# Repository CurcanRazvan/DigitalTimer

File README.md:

# Digital Timer - University Practice Project

This is the project I built for my 2nd-year university practice module. It is a digital timer designed in KiCad, capable of counting seconds (0-59) and displaying them on two 7-segment displays.

### Technical Overview

The circuit is designed with a modular approach:
1.  **Clock Signal:** Generated by an **NE555** timer configured as an astable oscillator.
2.  **Counting:** Handled by two **74LS193** 4-bit synchronous binary counters (U7 and U8).
3.  **Decoding & Display:** The binary signal is converted for the 7-segment displays using **CD4511** decoders.

**Logic Control:**
I used additional logic gates (**74LS73, 74LS08, CD4071**) to handle the counting limit (resetting at 60) and the Up/Down direction control.

### Schematic
Here is the final schematic, which includes the corrections needed for everything to work properly:

### v1.0 & Debugging

After getting the PCB manufactured and soldering the components, I spotted a mistake in the initial schematic: Pin 11 (Load) on the counters wasn't connected to 5V, and the C4 capacitor (47uF) wasn't linked to resistor R17.

**The Fix:**
I fixed this directly on the board by adding two jumper wires on the bottom layer.
* The red wires visible in the photo below connect the pins to 5V and route the capacitor correctly.
* With these changes, the circuit works perfectly.

| Top Layer (Components) | Bottom Layer (The Red Wire Fix) |
|:---:|:---:|
|  |  |

### Bill of Materials (BOM)

The total cost for the project (components + PCB + shipping) was approximately 140 Lei (~$30).

| Ref | Component | Description |
|:---|:---|:---|
| U9 | **NE555P** | Precision Timer |
| U7, U8 | **SN74LS193N** | Sync Binary Counter UP/DOWN |
| U6, U10 | **CD4511BE** | BCD to 7-Segment Decoder |
| U5, U11 | **HDSP-5601** | 7-Segment Display |
| U1 | **L7805** | 5V Voltage Regulator |
| U2 | **SN74LS73AN** | Dual JK Flip-Flop |
| U3 | **SN74LS08N** | Quad 2-Input AND Gate |
| U4 | **CD4071BE** | Quad 2-Input OR Gate |
| - | **9V Battery** | Power Source |

### Repository Structure
* `/kicad` - Source files (.sch, .kicad_pcb)
* `/img` - Images and renders

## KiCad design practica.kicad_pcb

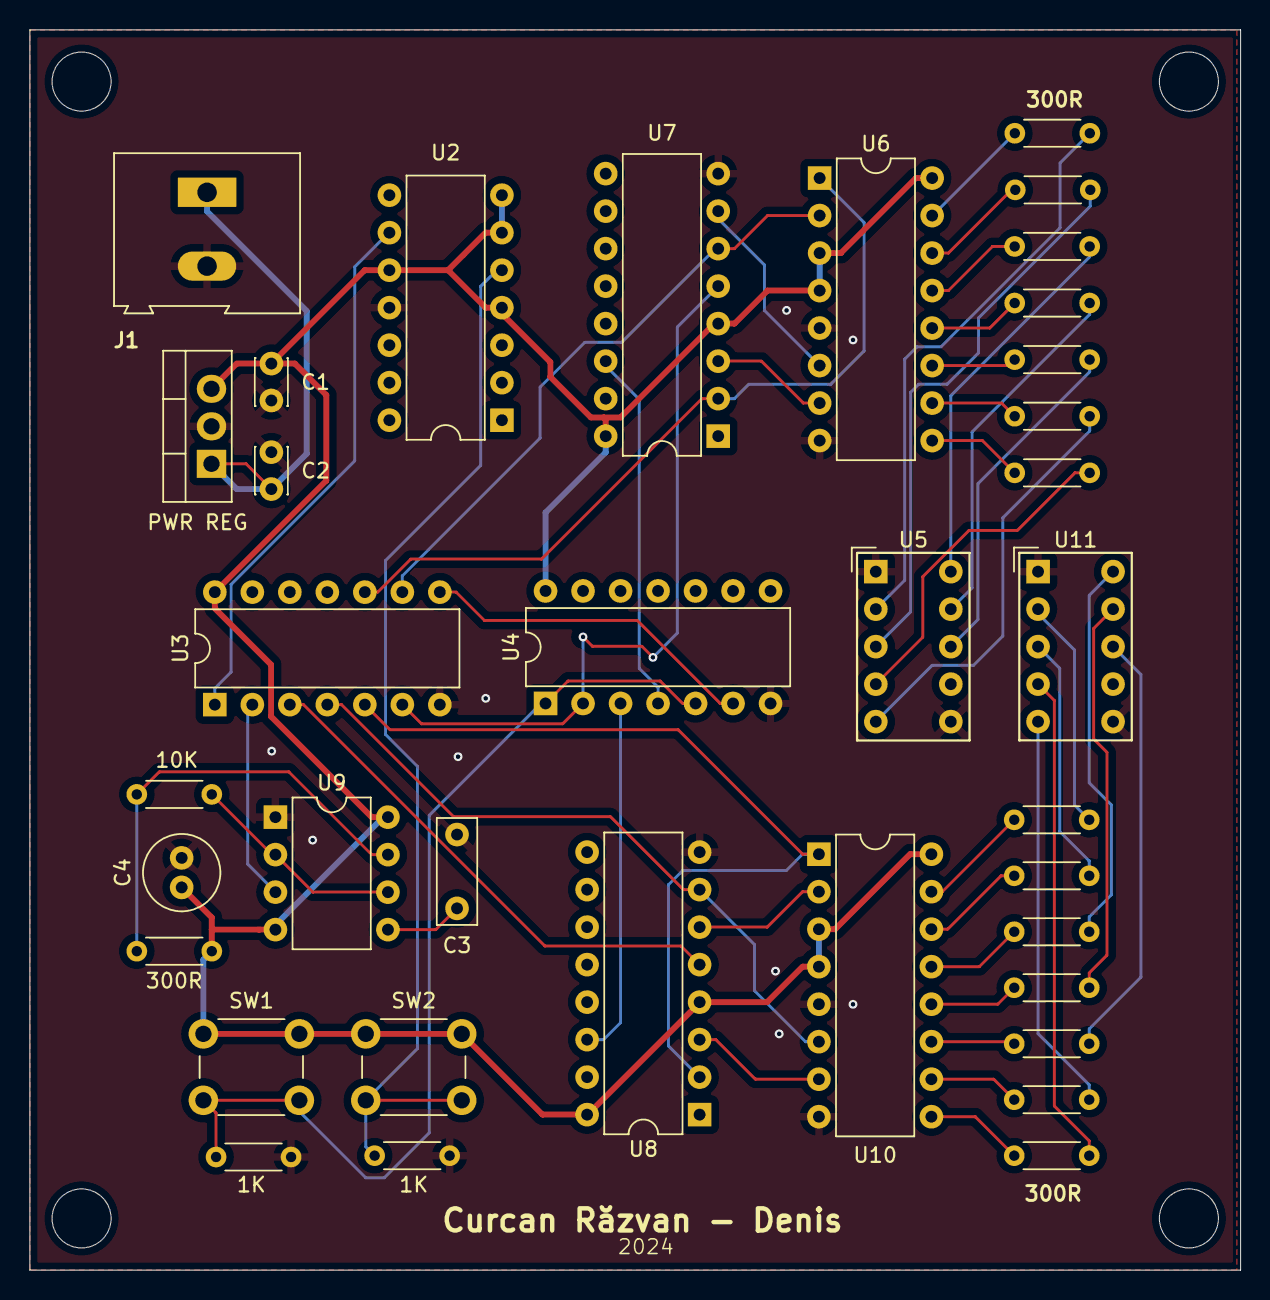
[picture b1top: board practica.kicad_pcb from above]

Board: 2 copper layers, 82.0 x 84.0 mm, 36 parts (0 on the bottom side), 51 nets.

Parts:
1K, 1K#2: 1k; R_Axial_DIN0204_L3.6mm_D1.6mm_P5.08mm_Horizontal
10K: 10k; R_Axial_DIN0204_L3.6mm_D1.6mm_P5.08mm_Horizontal
300R: 300; R_Axial_DIN0204_L3.6mm_D1.6mm_P5.08mm_Horizontal
C1, C2: 100n; C_Disc_D3.0mm_W2.0mm_P2.50mm
C3: 10n; C_Rect_L7.0mm_W2.5mm_P5.00mm
C4: 47u; C_Radial_D5.0mm_H11.0mm_P2.00mm
J1: Screw_Terminal_01x02; TerminalBlock_Altech_AK300-2_P5.00mm
PWR REG: L7805; TO-220-3_Vertical
R1, R2, R3, R4, R5, R6, R7, R8, R9, R10, R11, R12, R13, R14: 300R; R_Axial_DIN0204_L3.6mm_D1.6mm_P5.08mm_Horizontal
SW1: SW_Push; SW_PUSH_6mm
SW2: SW_Start_Stop; SW_PUSH_6mm
U2: 74LS73; DIP-14_W7.62mm
U3: 74LS08; DIP-14_W7.62mm
U4: 4071; DIP-14_W7.62mm
U5, U11: HDSP-7403; HDSP-7401
U6, U10: 4511; DIP-16_W7.62mm
U7, U8: 74LS193; DIP-16_W7.62mm
U9: NE555D; DIP-8_W7.62mm

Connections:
+5V: 300R.2, C1.1, C4.2, PWR REG.3 (OUT), SW1.1, SW2.1, U2.4 (VCC), U2.6 (~R), U2.7 (J), U2.10 (K), U3.14 (VCC), U4.14 (VDD), U6.3 (~LT), U6.4 (~BI), U6.16 (Vdd), U7.4 (DOWN), U7.16 (VCC), U8.4 (DOWN), U8.16 (VCC), U9.4 (R), U9.8 (VCC), U10.3 (~LT), U10.4 (~BI), U10.16 (Vdd)
GND: 1K.2, 1K#2.2, C1.2, C2.2, C3.1, C4.1, J1.2, PWR REG.2 (GND), U2.11 (GND), U3.7 (GND), U4.7 (VSS), U5.1 (CC), U5.6 (CC), U6.5 (~EL), U6.8 (Vss), U7.8 (GND), U8.8 (GND), U9.1 (GND), U10.5 (~EL), U10.8 (Vss), U11.1 (CC), U11.6 (CC)
unnamed: C2.1, J1.1, PWR REG.1 (IN)
unnamed: 1K.1, SW1.2, U4.1, U4.5
unnamed: 1K#2.1, SW2.2, U2.5 (C)
unnamed: U2.9 (Q), U3.1
unnamed: U3.8, U4.6
unnamed: R1.2, U5.10 (A)
unnamed: R2.2, U5.9 (B)
unnamed: R3.2, U5.8 (C)
unnamed: R4.2, U5.5 (D)
unnamed: R5.2, U5.4 (E)
unnamed: R6.2, U5.2 (F)
unnamed: R7.2, U5.3 (G)
unnamed: U6.7 (DA), U7.3 (QA)
unnamed: U3.10, U6.1 (DB), U7.2 (QB)
unnamed: U3.9, U6.2 (DC), U7.6 (QC)
unnamed: U6.6 (DD), U7.7 (QD)
unnamed: R1.1, U6.13 (Qa)
unnamed: R2.1, U6.12 (Qb)
unnamed: R3.1, U6.11 (Qc)
unnamed: R4.1, U6.10 (Qd)
unnamed: R5.1, U6.9 (Qe)
unnamed: R6.1, U6.15 (Qf)
unnamed: R7.1, U6.14 (Qg)
unnamed: U4.4, U7.14 (CLR)
unnamed: U3.6, U4.2, U7.5 (UP)
unnamed: U4.3, U8.14 (CLR)
unnamed: U3.3, U8.5 (UP)
unnamed: C3.2, U9.5 (CV)
unnamed: 10K.2, 300R.1, U9.7 (DIS)
unnamed: U3.2, U9.3 (Q)
unnamed: 10K.1, U9.2 (TR), U9.6 (THR)
unnamed: U8.3 (QA), U10.7 (DA)
unnamed: U3.5, U8.2 (QB), U10.1 (DB)
unnamed: U8.6 (QC), U10.2 (DC)
unnamed: U3.4, U8.7 (QD), U10.6 (DD)
unnamed: R8.1, U10.13 (Qa)
unnamed: R9.1, U10.12 (Qb)
unnamed: R10.1, U10.11 (Qc)
unnamed: R11.1, U10.10 (Qd)
unnamed: R12.1, U10.9 (Qe)
unnamed: R13.1, U10.15 (Qf)
unnamed: R14.1, U10.14 (Qg)
unnamed: R8.2, U11.10 (A)
unnamed: R9.2, U11.9 (B)
unnamed: R10.2, U11.8 (C)
unnamed: R11.2, U11.5 (D)
unnamed: R12.2, U11.4 (E)
unnamed: R13.2, U11.2 (F)
unnamed: R14.2, U11.3 (G)

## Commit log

2026-02-13 Initial commit - 2nd year practice project
2026-02-13 Added project images
2026-02-13 Add README with project details and specifications
    Added detailed project description, technical specifications, electrical schematic, debugging iteration, materials list, and repository structure.
2026-02-13 README update content
2026-02-13 Revise README for clarity and technical details
    Updated project description and technical overview for clarity. Adjusted details about counting capabilities and logic components used.
